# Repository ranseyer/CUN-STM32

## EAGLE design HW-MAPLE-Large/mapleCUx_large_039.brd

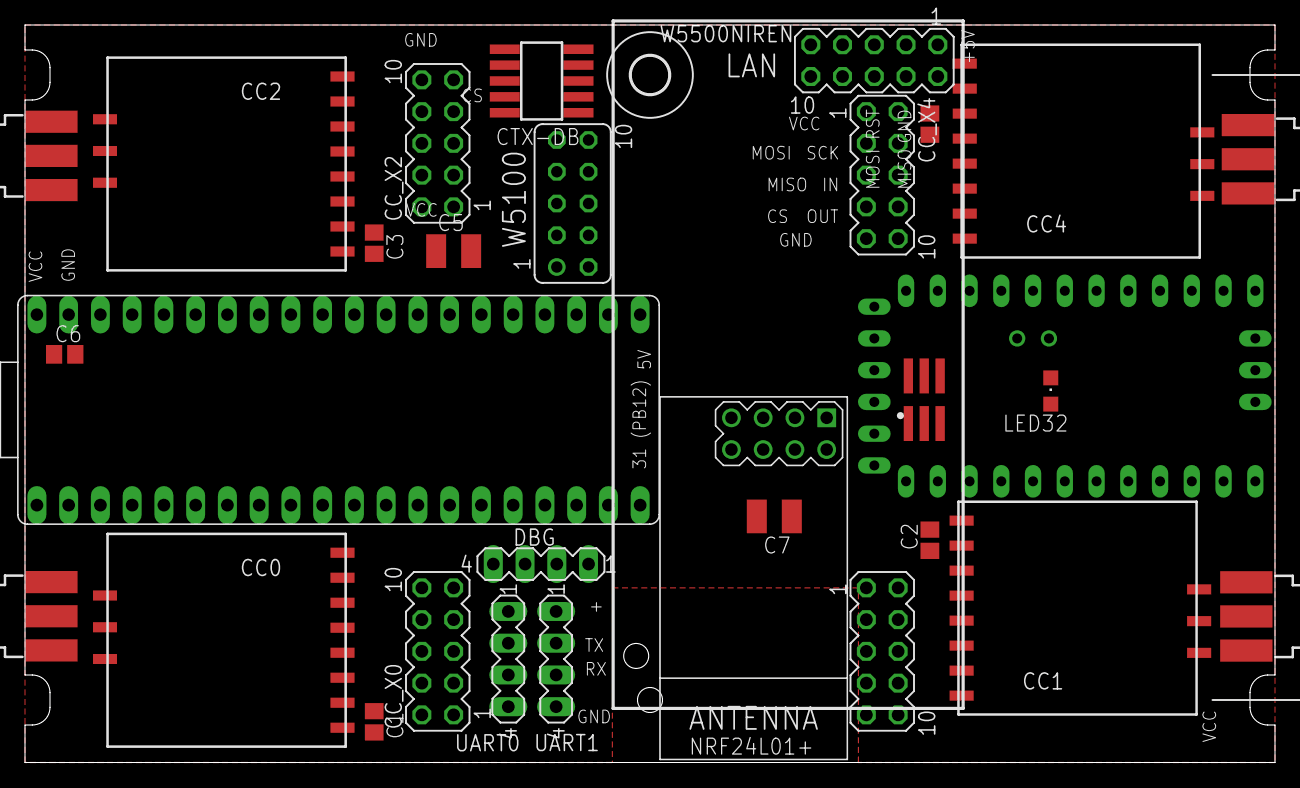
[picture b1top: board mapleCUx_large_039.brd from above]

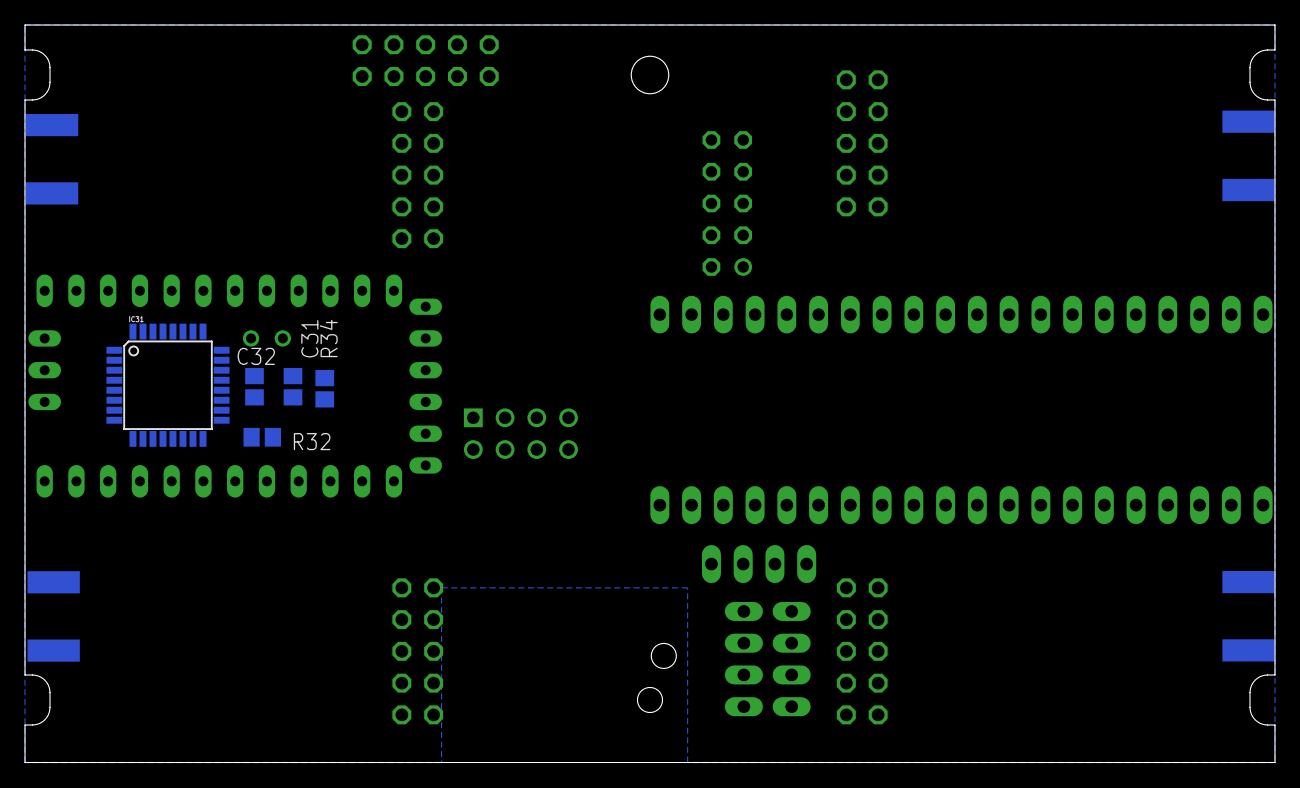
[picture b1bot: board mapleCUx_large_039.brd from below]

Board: 2 copper layers, 100.0 x 59.0 mm, 36 parts (5 on the bottom side), 48 nets, no tracks yet.

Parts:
C1, C2, C3, C4, C6: 22pF; C0805
C5: 10uF; C1210
C7: 4,7; C1210
C31, C32: 100n; C0805
CC0, CC1, CC2, CC4: CC1101_MODULE1SMD; CC1101_MODULE1_SMD
CC_X0, CC_X1, CC_X2, CC_X4: MA05-2
CTX-DB: 1365-10
DBG: MA04-1
H6: MOUNT-HOLE3.0; 3,0
IC31: ATMEGA168-TQFP; TQFP32-08
LED32: CHIPLED_0805
NRF24L01+: NRF24L01+; WIRELESS-NRF24L01
R32: 1k; R0805
R34: R0805
U$1: MAPLEMINI; 20-DIP
U$2: ABK-PRO-MINI
UART0, UART1: MA04-1
W5100: FE05-2
W5500NIREN: MA05-2
X1, X2, X3, X4: SMA
X31: M03X2; 2X03-1.27MM_SMD

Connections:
+5V: U$1.21, W5100.1, W5500NIREN.1
CC_CS0: CC0.CSN, CC_X0.7, U$1.29
CC_CS1: CC1.CSN, CC_X1.7, U$1.35
CC_CS2: CC2.CSN, CC_X2.7, U$1.4
CC_CS3: CC4.CSN, CC_X4.7, U$1.25
CC_IN_0: CC0.GDO2, CC_X0.6, U$1.33
CC_IN_1: CC1.GDO2, CC_X1.6, U$1.7
CC_IN_2: CC2.GDO2, CC_X2.6, U$1.5
CC_IN_3: CC4.GDO2, CC_X4.6, U$1.37
CC_OUT_0: CC0.GDO0, CC_X0.8, U$1.32
CC_OUT_1: CC1.GDO0, CC_X1.8, U$1.6
CC_OUT_2: CC2.GDO0, CC_X2.8, U$1.36
CE-A: IC31.13, NRF24L01+.3, U$2.D9
CSN-A: IC31.14, NRF24L01+.4, U$2.D10
GND: C1.1, C2.1, C3.1, C4.1, C5.2, C6.2, C7.1, C31.2, C32.2, CC0.GND@0, CC0.GND@1, CC0.GND@2, CC1.GND@0, CC1.GND@1, CC1.GND@2, CC2.GND@0, CC2.GND@1, CC2.GND@2, CC4.GND@0, CC4.GND@1, CC4.GND@2, CC_X0.9, CC_X0.10, CC_X1.9, CC_X1.10, CC_X2.9, CC_X2.10, CC_X4.9, CC_X4.10, CTX-DB.3, CTX-DB.5, DBG.4, IC31.3, IC31.5, IC31.21, LED32.C, NRF24L01+.1, U$1.24, U$1.39, U$2.GND, UART0.4, UART1.4, W5100.2, W5100.7, W5500NIREN.3, X1.GND@1, X1.GND@2, X1.GND@3, X1.GND@4, X2.GND@1, X2.GND@2, X2.GND@3, X2.GND@4, X3.GND@1, X3.GND@2, X3.GND@3, X3.GND@4, X4.GND@1, X4.GND@2, X4.GND@3, X4.GND@4, X31.P$6
IRQ-A: IC31.32, NRF24L01+.8, U$2.D2
M-RES: IC31.29, R34.2, X31.P$5
M-SCK: IC31.17, X31.P$3
MISO1: CC0.MISO, CC1.MISO, CC2.MISO, CC4.MISO, CC_X0.5, CC_X1.5, CC_X2.5, CC_X4.5, U$1.27
MISO2: U$1.18, W5100.8, W5500NIREN.4
MISO-A: IC31.16, NRF24L01+.7, U$2.D12, X31.P$1
MOSI1: CC0.MOSI, CC1.MOSI, CC2.MOSI, CC4.MOSI, CC_X0.3, CC_X1.3, CC_X2.3, CC_X4.3, U$1.26
MOSI-A: IC31.15, NRF24L01+.6, U$2.D11, X31.P$4
unnamed: CC2.ANT, X3.1
unnamed: CC4.ANT, X4.1
unnamed: CC1.ANT, X1.1
unnamed: CC0.ANT, X2.1
unnamed: LED32.A, R32.2
unnamed: C32.1, IC31.20
NRESET: CTX-DB.10, U$1.34
RST: U$1.17, W5100.5, W5500NIREN.6
RX1: U$1.22, UART1.3
RX-MAPLE: IC31.31, U$1.30, U$2.TX0-1, UART0.3
RX_DBG: DBG.3, U$1.14
RX_LED: IC31.2, R32.1
SCK1: CC0.SCLK, CC1.SCLK, CC2.SCLK, CC4.SCLK, CC_X0.4, CC_X1.4, CC_X2.4, CC_X4.4, U$1.28
SCK2: U$1.19, W5100.6, W5500NIREN.10
SCK-A: NRF24L01+.5, U$2.D13
SWCLK/TCK: CTX-DB.4, U$1.10
SWDIO/TMS: CTX-DB.2, U$1.11
SWO/TDO: CTX-DB.6, U$1.8
TDI: CTX-DB.8, U$1.9
TX1: U$1.23, UART1.2
TX-MAPLE: IC31.30, U$1.31, U$2.RX1-1, UART0.2
TX_DBG: DBG.2, U$1.15
VCC: C1.2, C2.2, C3.2, C4.2, C5.1, C6.1, C7.2, C31.1, CC0.VCC, CC1.VCC, CC2.VCC, CC4.VCC, CC_X0.1, CC_X0.2, CC_X1.1, CC_X1.2, CC_X2.1, CC_X2.2, CC_X4.1, CC_X4.2, CTX-DB.1, DBG.1, IC31.4, IC31.6, IC31.18, NRF24L01+.2, R34.1, U$1.40, U$2.VCC, UART0.1, UART1.1, X31.P$2
WIZ_CS: U$1.20, W5100.3, W5500NIREN.8
WIZ_RST: U$1.16, W5100.4, W5500NIREN.5

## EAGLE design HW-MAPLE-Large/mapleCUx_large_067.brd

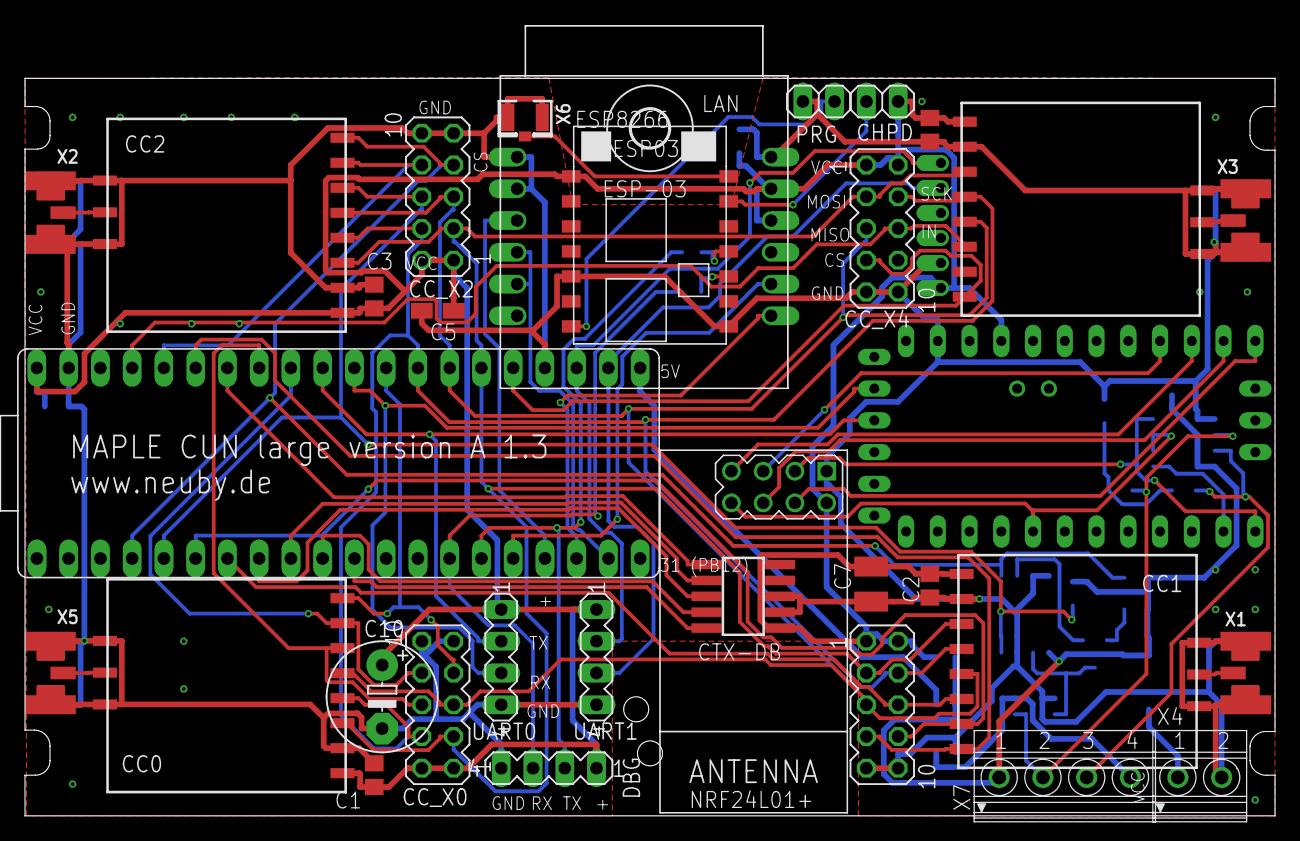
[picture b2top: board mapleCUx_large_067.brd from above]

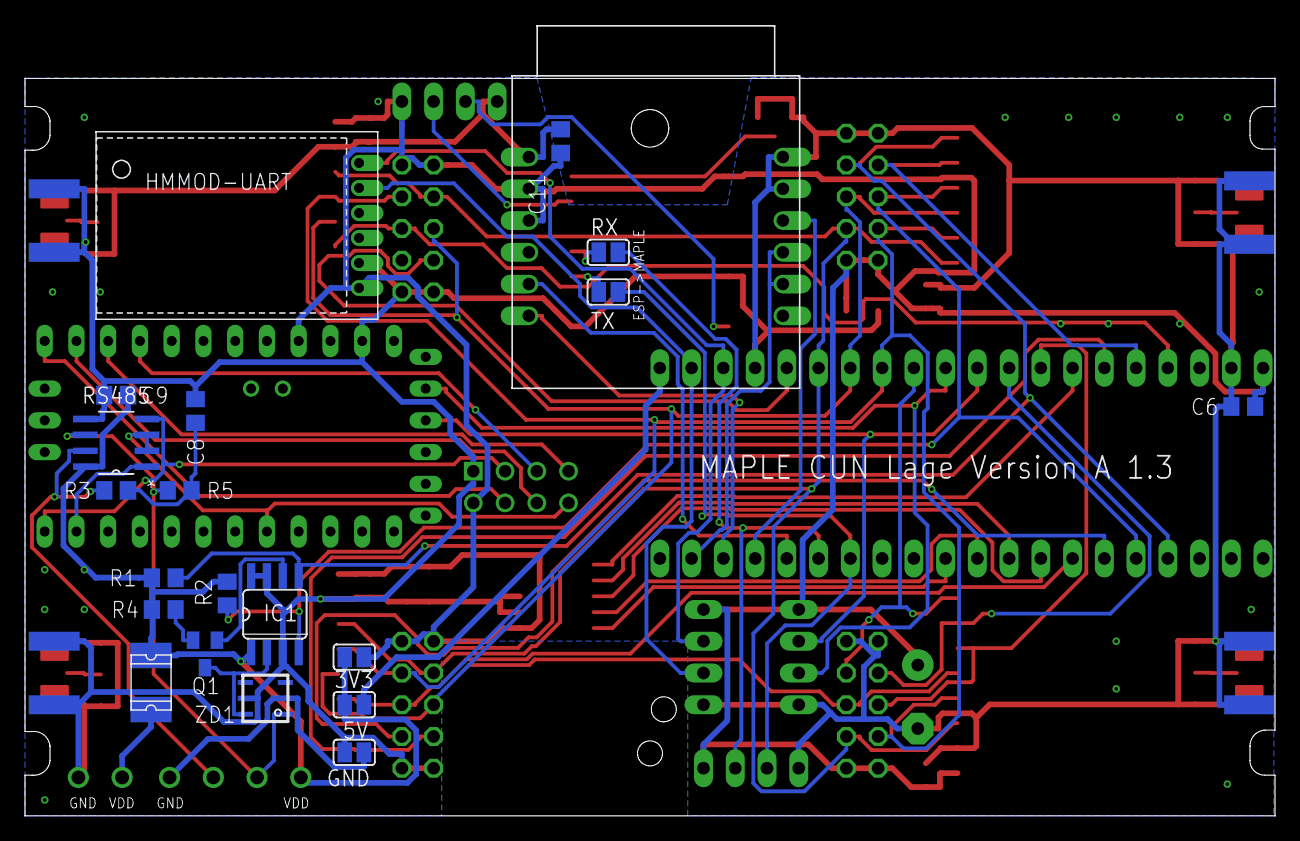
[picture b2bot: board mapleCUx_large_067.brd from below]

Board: 2 copper layers, 100.0 x 63.2 mm, 54 parts (20 on the bottom side), 57 nets.

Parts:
3V3, 5V: SJ
C1, C2, C3, C4, C6, C11: 22pF; C0805
C5: 10uF; R/2012-12W
C7: 4,7; C1210
C8: 220p; C0805
C9: 22p; C0805
C10: 100uF; E5-8,5
CC0: CC1101; CC1101_MODULE1_SMD
CC1, CC2, CC4: CC1101_MODULE1SMD; CC1101_MODULE1_SMD
CC_X0, CC_X1, CC_X2, CC_X4: MA05-2
CHPD: 1X02
CTX-DB: 1365-10
DBG: MA04-1
ESP8266: ESP03
F1: 1812L
GND: SJ
H6: MOUNT-HOLE3.0; 3,0
HMMOD-UART: HM-MOD-UARTDIL; HM-MOD-UART-DIL
IC1: DS2482-100S; SO08
IC2: LAN-USR-ES1; USR-ES1
NRF24L01+: NRF24L01+; WIRELESS-NRF24L01
PRG: 1X02
Q1: BSS84; SOT23
R1: 4k7; R0805
R2: 4K7; R0805
R3, R5: 60; R0805
R4: 100; R0805
RS485: MAX487ECSA+; SOIC127P600X175-8N
RX: SJ
TX: SJ
U$1: MAPLEMINI; 20-DIP
U$2: ABK-PRO-MINI
UART0, UART1: MA04-1
X1, X2, X3, X5: SMA_EDGELAUNCH_UFL
X4: 1751248
X6: U.FL
X7: 1751264
ZD1: DS9503P; TSOC6

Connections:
1W: R5.2, RS485.6, X7.2, ZD1.1
2W: R3.2, RS485.7, X7.3
+5V: 5V.2, U$1.21
CC_CS0: CC0.CSN, CC_X0.7, U$1.29
CC_CS1: CC1.CSN, CC_X1.7, U$1.35
CC_CS2: CC2.CSN, CC_X2.7, IC1.5, R1.2, U$1.4
CC_CS3: CC4.CSN, CC_X4.7, U$1.25
CC_IN_0: CC0.GDO2, CC_X0.6, U$1.33
CC_IN_1: CC1.GDO2, CC_X1.6, U$1.7
CC_IN_2: CC2.GDO2, CC_X2.6, IC1.4, R2.2, U$1.5
CC_IN_3: CC4.GDO2, CC_X4.6, U$1.37
CC_OUT_0: CC0.GDO0, CC_X0.8, U$1.32
CC_OUT_1: CC1.GDO0, CC_X1.8, U$1.6
CC_OUT_2: CC2.GDO0, CC_X2.8, U$1.36
CE-A: NRF24L01+.3, RS485.4, U$2.D9
CSN-A: NRF24L01+.4, U$2.D10
GD: GND.2, X7.4, ZD1.2
GND: C1.1, C2.1, C3.1, C4.1, C5.-, C6.2, C7.1, C8.2, C9.1, C10.-, C11.1, CC0.GND@0, CC0.GND@1, CC0.GND@2, CC1.GND@0, CC1.GND@1, CC1.GND@2, CC2.GND@0, CC2.GND@1, CC2.GND@2, CC4.GND@0, CC4.GND@1, CC4.GND@2, CC_X0.9, CC_X0.10, CC_X1.9, CC_X1.10, CC_X2.9, CC_X2.10, CC_X4.9, CC_X4.10, CTX-DB.3, CTX-DB.5, DBG.4, ESP8266.GND, ESP8266.GPIO15, GND.1, HMMOD-UART.2, IC1.3, IC1.7, IC1.8, IC2.1, IC2.2, IC2.12, NRF24L01+.1, PRG.2, RS485.5, U$1.24, U$1.39, U$2.GND, UART0.4, UART1.4, X1.GND@1, X1.GND@2, X1.GND@3, X1.GND@4, X2.GND@1, X2.GND@2, X2.GND@3, X2.GND@4, X3.GND@1, X3.GND@2, X3.GND@3, X3.GND@4, X4.2, X5.GND@1, X5.GND@2, X5.GND@3, X5.GND@4, X6.1, X6.2, ZD1.5
IRQ-A: NRF24L01+.8, RS485.2, RS485.3, U$2.D2
MISO1: CC0.MISO, CC1.MISO, CC2.MISO, CC4.MISO, CC_X0.5, CC_X1.5, CC_X2.5, CC_X4.5, U$1.27
MISO2: IC2.7, U$1.18
MISO-A: NRF24L01+.7, U$2.D12
MOSI1: CC0.MOSI, CC1.MOSI, CC2.MOSI, CC4.MOSI, CC_X0.3, CC_X1.3, CC_X2.3, CC_X4.3, U$1.26
MOSI-A: NRF24L01+.6, U$2.D11
unnamed: CC1.ANT, X1.P
unnamed: CC4.ANT, X3.P
unnamed: CC2.ANT, X2.P
unnamed: CC0.ANT, X5.P
unnamed: ESP8266.GPIO0, PRG.1
unnamed: ESP8266.ANT, X6.3
unnamed: CHPD.2, ESP8266.CH_PD
unnamed: ESP8266.URXD, RX.2
unnamed: ESP8266.UTXD, TX.2
unnamed: C8.1, R3.1, R5.1
unnamed: F1.P$2, X4.1
unnamed: IC1.6, Q1.1
unnamed: IC1.2, Q1.3, ZD1.6
unnamed: Q1.2, R4.1
NRESET: CTX-DB.10, U$1.34
RO-A: RS485.1, U$2.D8
RST: IC2.3, U$1.17
RX1: HMMOD-UART.5, U$1.22, UART1.3
RX-MAPLE: U$1.30, U$2.TX0-1, UART0.3
RX_DBG: DBG.3, TX.1, U$1.14
SCK1: CC0.SCLK, CC1.SCLK, CC2.SCLK, CC4.SCLK, CC_X0.4, CC_X1.4, CC_X2.4, CC_X4.4, U$1.28
SCK2: IC2.4, IC2.5, U$1.19
SCK-A: NRF24L01+.5, U$2.D13
SWCLK/TCK: CTX-DB.4, U$1.10
SWDIO/TMS: CTX-DB.2, U$1.11
SWO/TDO: CTX-DB.6, U$1.8
TDI: CTX-DB.8, U$1.9
TX1: HMMOD-UART.6, U$1.23, UART1.2
TX-MAPLE: U$1.31, U$2.RX1-1, UART0.2
TX_DBG: DBG.2, RX.1, U$1.15
VCC: 3V3.1, C1.2, C2.2, C3.2, C4.2, C5.+, C6.1, C7.2, C10.+, C11.2, CC0.VCC, CC1.VCC, CC2.VCC, CC4.VCC, CC_X0.1, CC_X0.2, CC_X1.1, CC_X1.2, CC_X2.1, CC_X2.2, CC_X4.1, CC_X4.2, CHPD.1, CTX-DB.1, DBG.1, ESP8266.VCC, HMMOD-UART.1, IC2.10, IC2.11, NRF24L01+.2, U$1.40, U$2.VCC, UART0.1, UART1.1
VDD: 3V3.2, 5V.1, C9.2, F1.P$1, IC1.1, R1.1, R2.1, R4.2, RS485.8, X7.1
WIZ_RST: IC2.8, U$1.16

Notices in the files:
parts and their libraries:
diy-modules: Released under the Creative Commons Attribution 4.0 International License: http://creativecommons.org/licenses/by/4.0
